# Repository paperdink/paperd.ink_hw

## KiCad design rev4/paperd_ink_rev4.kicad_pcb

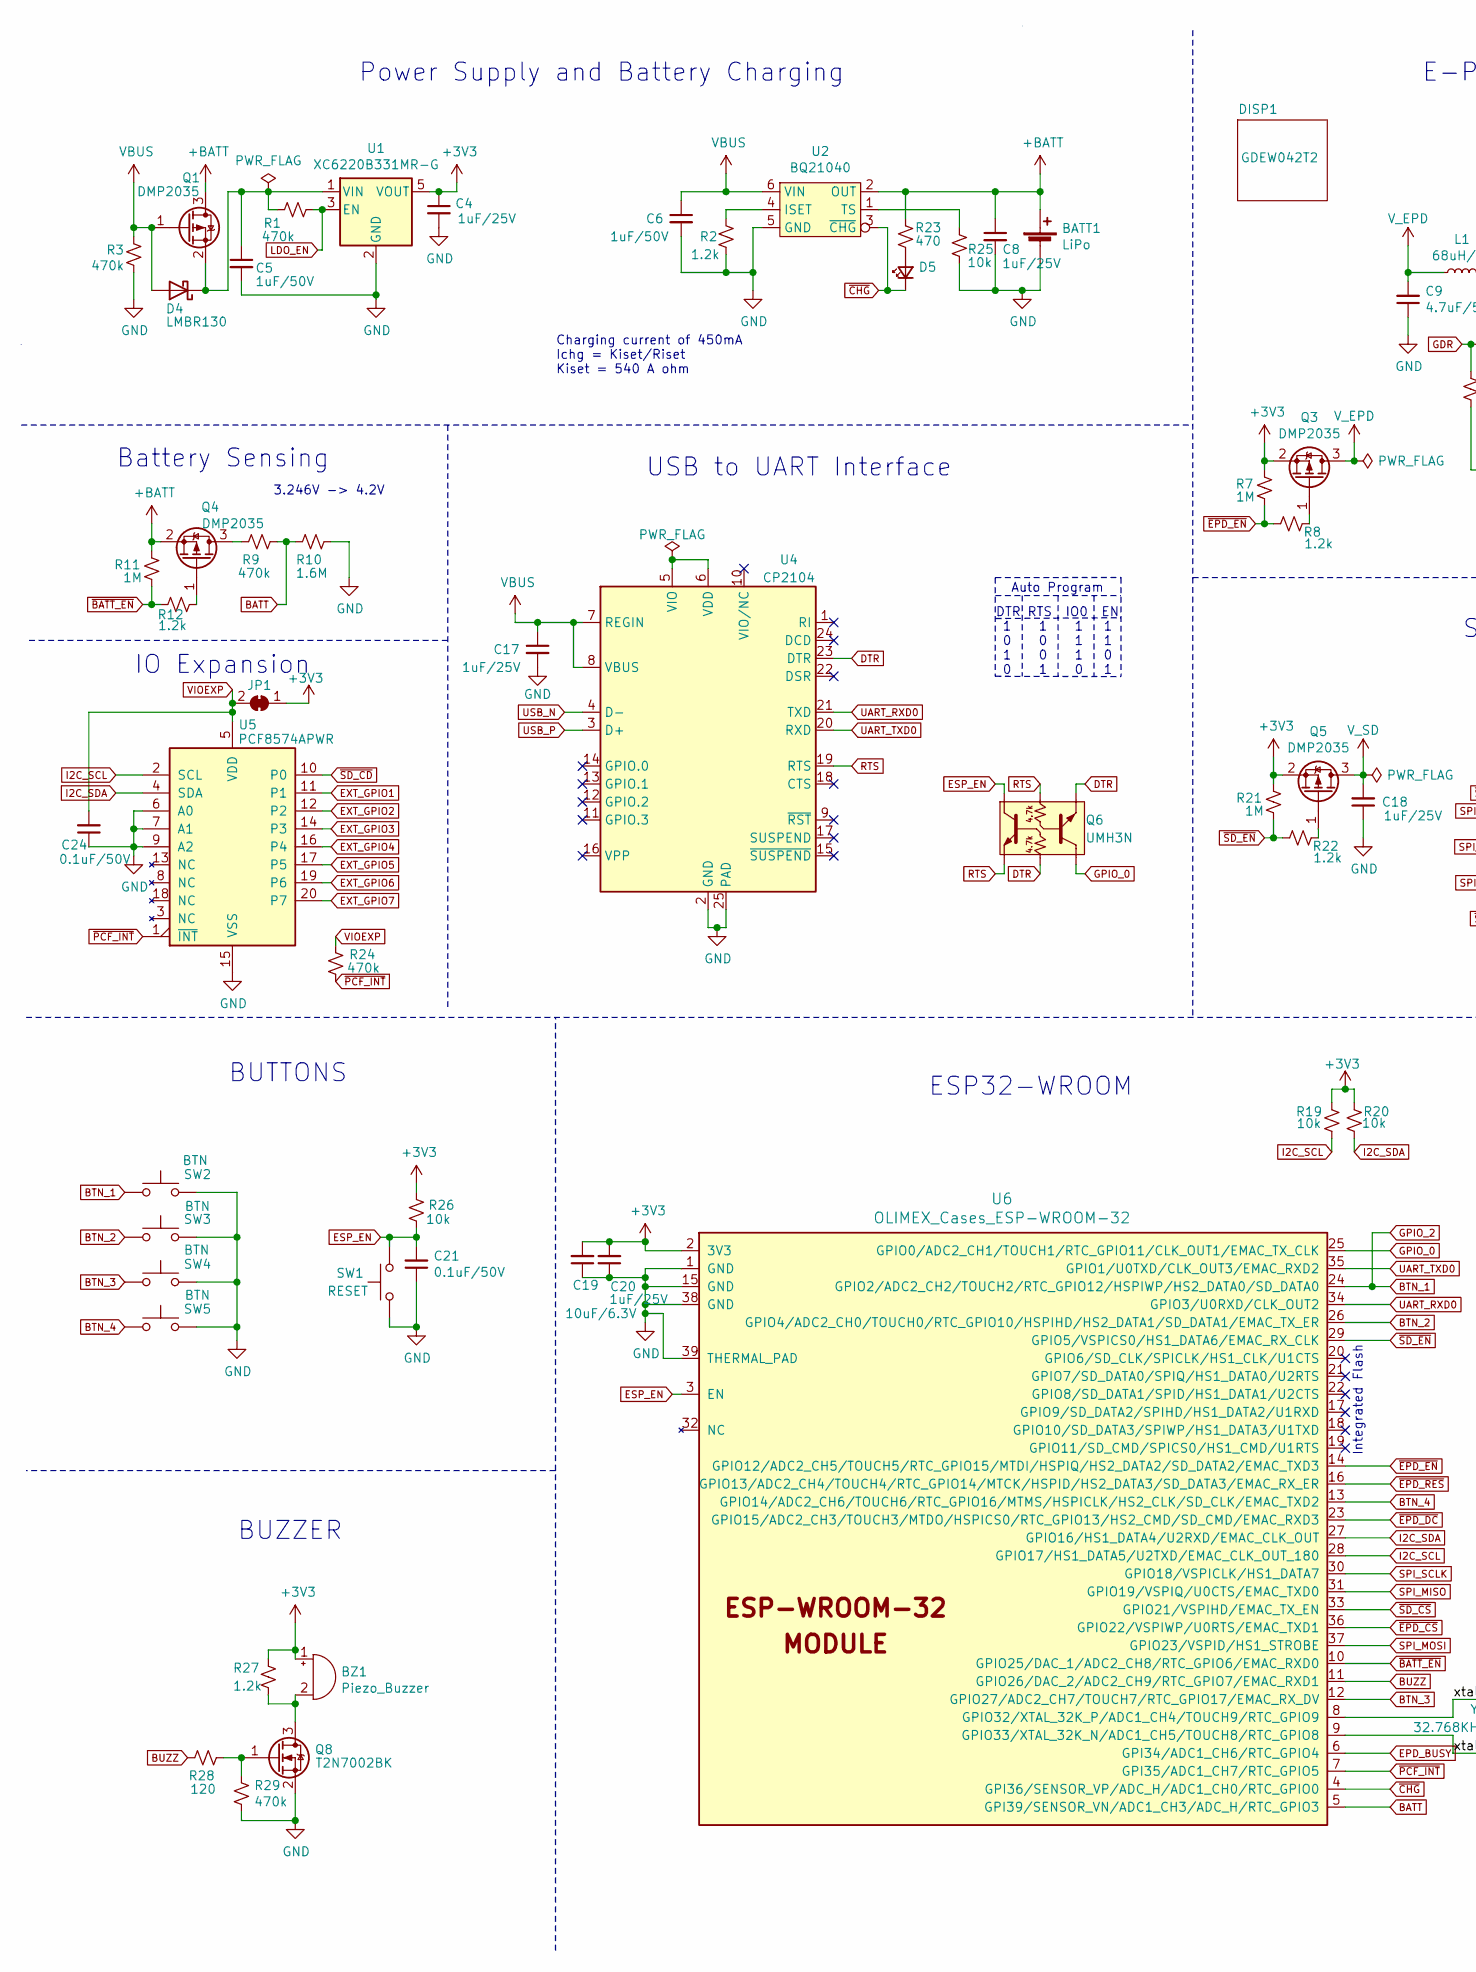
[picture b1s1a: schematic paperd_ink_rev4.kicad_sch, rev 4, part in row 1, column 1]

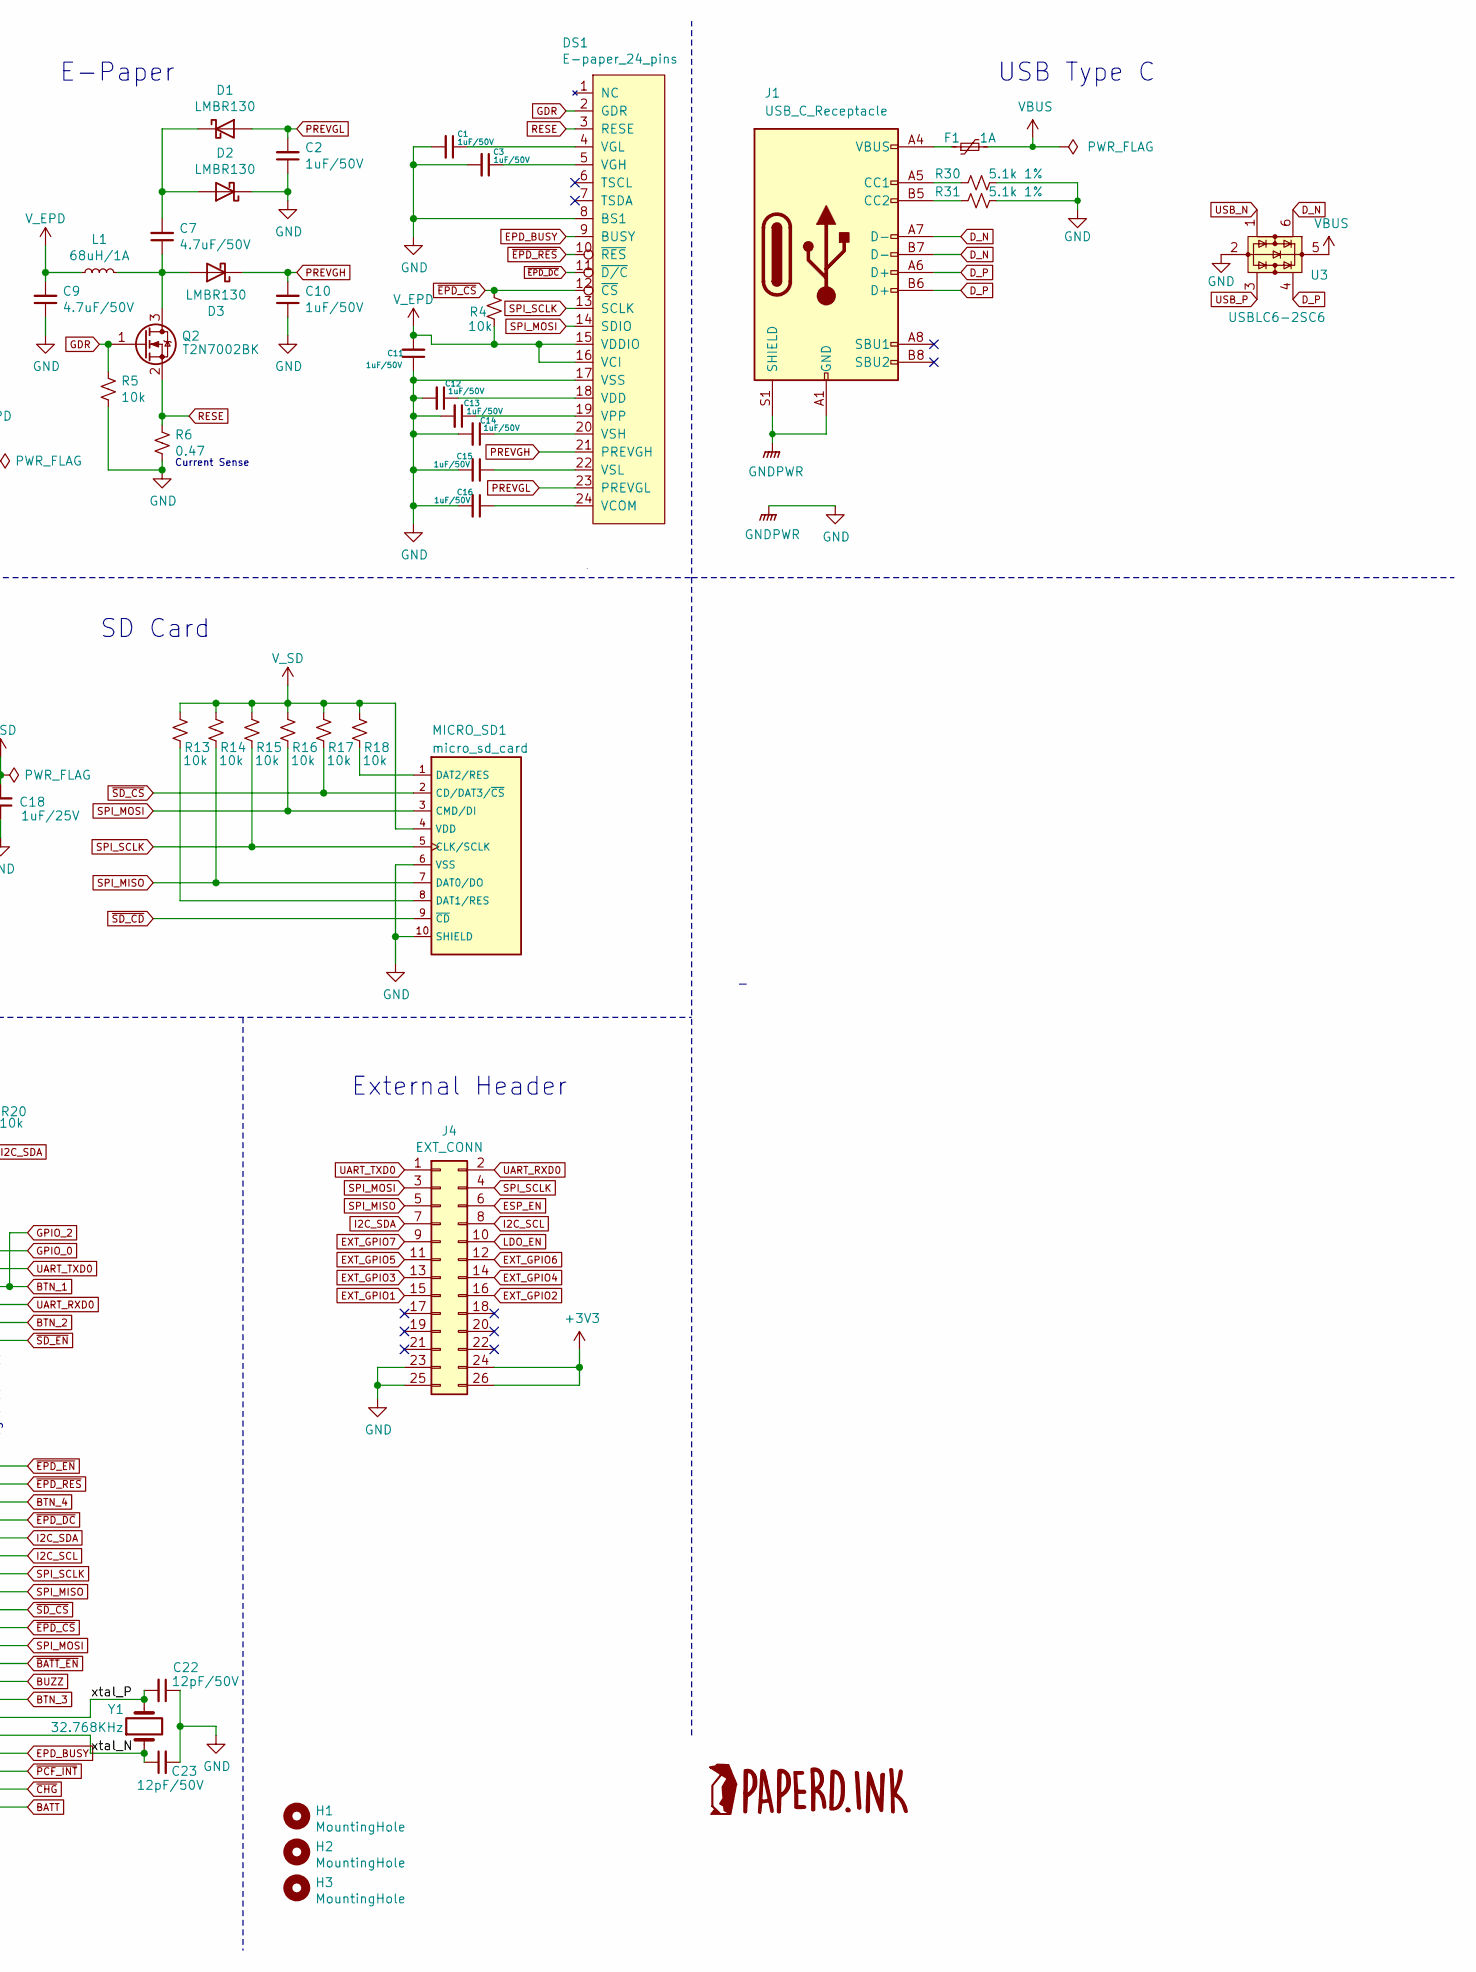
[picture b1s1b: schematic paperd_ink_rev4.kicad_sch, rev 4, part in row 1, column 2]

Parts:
BATT1: LiPo; JST_PH_B2B-PH-SM4-TB_1x02-1MP_P2.00mm_Vertical; MPN C47647; LCSC C47647
BZ1: Piezo_Buzzer; KLJ-1230; MPN KLJ-1230; LCSC C201042
C1, C2, C3, C5, C6, C10, C11, C12, C13, C14, C15, C16: 1uF/50V; C_0603_1608Metric; MPN CL10A105KB8NNNC; LCSC C15849
C4, C8, C17, C18, C20: 1uF/25V; C_0402_1005Metric; MPN CL05A105KA5NQNC; LCSC C52923
C7, C9: 4.7uF/50V; C_0805_2012Metric; MPN CL21A475KBQNNNE; LCSC C98192
C19: 10uF/6.3V; C_0402_1005Metric; MPN CL05A106MQ5NUNC; LCSC C15525
C21, C24: 0.1uF/50V; C_0402_1005Metric; MPN CC0402KRX5R9BB104; LCSC C105882
C22, C23: 12pF/50V; C_0402_1005Metric; MPN 0402CG120J500NT; LCSC C1547
D1, D2, D3, D4: LMBR130; D_SOD-123; MPN LMBR130T1G; LCSC C48974
D5: LED_Small; TJ-S1706SW6TGLC2R-A5; MPN TJ-S1706SW6TGLC2R-A5; LCSC C273612
DISP1: GDEW042T2; MPN GDEW042T2
DS1: E-paper_24_pins; 24 pin FPC connector; MPN 0.5-24P XGXJ-H2.0 119; LCSC C2858298
F1: 1A; Fuse_0805_2012Metric; MPN MF-PSMF050X-2; LCSC C116170
H1, H2, H3: MountingHole; JLCPCB_Tooling_Hole
J1: USB_C_Receptacle; USB_C_Receptacle_HRO_TYPE-C-31-M-12; MPN 918-418K2023S40019; LCSC C709035
J4: EXT_CONN; PinHeader_2x13_P2.54mm_Vertical_SMD; MPN DNP
JP1: IO_EXP_JMP; SolderJumper-2_P1.3mm_Bridged_RoundedPad1.0x1.5mm; MPN DNP
L1: 68uH/1A; L_1210_3225Metric; MPN CBC3225T680MR; LCSC C223227
MICRO_SD1: micro_sd_card; HYC77-TF09-200; MPN HYC77-TF09-200; LCSC C341092
Q1, Q3, Q4, Q5: DMP2035; SOT-23; MPN DMP2035U-7; LCSC C110499
Q2, Q8: T2N7002BK; SOT-23; MPN T2N7002BK,LM; LCSC C146372
Q6: UMH3N; SOT-363_SC-70-6; MPN UMH3N; LCSC C62892
R1, R3, R9, R24, R29: 470k; R_0402_1005Metric; MPN WR04X4703FTL; LCSC C168230
R2, R8, R12, R22, R27: 1.2k; R_0402_1005Metric; MPN WR04X122JTL; LCSC C170376
R4, R5, R13, R14, R15, R16, R17, R18, R19, R20, R25, R26: 10k; R_0402_1005Metric; MPN RMS04JT103; LCSC C208959
R6: 0.47; R_0603_1608Metric; MPN 0603WAF470LT5E; LCSC C23411
R7, R11, R21: 1M; R_0402_1005Metric; MPN RMS04FT1004; LCSC C208777
R10: 1.6M; R_0402_1005Metric; MPN AC0402FR-071M6L; LCSC C226874
R23: 470; R_0402_1005Metric; MPN 0402WGJ0471TCE; LCSC C25167
R28: 120; R_0402_1005Metric; MPN WR04X1200FTL; LCSC C168196
R30, R31: 5.1k 1%; R_0402_1005Metric; MPN WR04X5101FTL; LCSC C163833
SW1: RESET; K2-1822SA-A3DW-06; MPN K2-1822SA-A3DW-06; LCSC C128937
SW2, SW3, SW4, SW5: BTN; TS36CA-0.7; MPN TS36CA-0.7; LCSC C412365
U1: XC6220B331MR-G; SOT-23-5; MPN XC6220B331MR-G; LCSC C86534
U2: BQ21040; SOT-23-6; MPN BQ21040DBVR; LCSC C202311
U3: USBLC6-2SC6; SOT-23-6; MPN USBLC6-2SC6; LCSC C558442
U4: CP2104; QFN-24-1EP_4x4mm_P0.5mm_EP2.6x2.6mm; MPN CP2104-F03-GMR; LCSC C47742
U5: PCF8574APWR; TSSOP-20_4.4x6.5mm_P0.65mm; MPN PCF8574TS/3,118; LCSC C57790
U6: OLIMEX_Cases_ESP-WROOM-32; ESP32-WROOM-32; MPN ESP32-WROOM-32D; LCSC C473012
Y1: 32.768KHz; Q13FC1350000400; MPN Q13FC1350000400; LCSC C32346

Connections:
+3V3: BZ1.1 (-), C4.1, C19.2, C20.2, J4.24, J4.26, JP1.1 (A), Q3.2 (S), Q5.2 (S), R7.2, R19.2, R20.2, R21.2, R26.1, R27.1, U1.5 (VOUT), U6.2 (3V3)
+BATT: BATT1.1 (+), C8.1, Q1.3 (D), Q4.2 (S), R11.2, R23.1, U2.2 (OUT)
/xtal_N: C23.1, U6.9 (GPIO33/XTAL_32K_N/ADC1_CH5/TOUCH8/RTC_G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), Y1.1
/xtal_P: C22.2, U6.8 (GPIO32/XTAL_32K_P/ADC1_CH4/TOUCH9/RTC_G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), Y1.2
BATT: R9.1, R10.2, U6.5 (GPI39/SENSOR_VN/ADC1_CH3/ADC_H/RTC_GPIO3)
BTN_1: SW2.2, U6.24 (GPIO2/ADC2_CH2/TOUCH2/RTC_GPIO12/HSPIWP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)
BTN_2: SW3.2, U6.26 (GPIO4/ADC2_CH0/TOUCH0/RTC_GPIO10/HSPIHD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)
BTN_3: SW4.2, U6.12 (GPIO27/ADC2_CH7/TOUCH7/RTC_GPIO17/EMAC_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)
BTN_4: SW5.2, U6.13 (GPIO14/ADC2_CH6/TOUCH6/RTC_GPIO16/MTMS/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)
BUZZ: R28.2, U6.11 (GPIO26/DAC_2/ADC2_CH9/RTC_GPIO7/EMAC_RX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)
DTR: Q6.2 (B1), Q6.4 (E2), U4.23 (DTR)
D_N: J1.A7 (D-), J1.B7 (D-), U3.6 (IO1)
D_P: J1.A6 (D+), J1.B6 (D+), U3.4 (IO2)
EPD_BUSY: DS1.9 (BUSY), U6.6 (GPI34/ADC1_CH6/RTC_GPIO4)
ESP_EN: C21.2, J4.6, Q6.6 (C1), R26.2, SW1.2, U6.3 (EN)
EXT_GPIO1: J4.15, U5.11 (P1)
EXT_GPIO2: J4.16, U5.12 (P2)
EXT_GPIO3: J4.13, U5.14 (P3)
EXT_GPIO4: J4.14, U5.16 (P4)
EXT_GPIO5: J4.11, U5.17 (P5)
EXT_GPIO6: J4.12, U5.19 (P6)
EXT_GPIO7: J4.9, U5.20 (P7)
GDR: DS1.2 (GDR), Q2.1 (G), R5.1
GND: BATT1.2 (-), C1.2, C2.1, C3.2, C4.2, C5.2, C6.2, C8.2, C9.1, C10.1, C11.1, C12.2, C13.2, C14.2, C15.2, C16.2, C17.2, C18.1, C19.1, C20.1, C21.1, C22.1, C23.2, C24.1, D2.1 (K), DS1.8 (BS1), DS1.17 (VSS), J1.A1 (GND), J1.A12 (GND), J1.B1 (GND), J1.B12 (GND), J1.S1 (SHIELD), J4.23, J4.25, MICRO_SD1.6 (VSS), MICRO_SD1.10 (SHIELD), Q8.2 (S), R2.2, R3.2, R5.2, R6.2, R10.1, R25.2, R29.2, R30.1, R31.1, SW1.1, SW2.1, SW3.1, SW4.1, SW5.1, U1.2 (GND), U2.5 (GND), U3.2 (GND), U4.2 (GND), U4.25 (PAD), U5.6 (A0), U5.7 (A1), U5.9 (A2), U5.15 (VSS), U6.1 (GND), U6.15 (GND), U6.38 (GND), U6.39 (THERMAL_PAD)
GPIO_0: Q6.3 (C2), U6.25 (GPIO0/ADC2_CH1/TOUCH1/RTC_GPIO11/CLK_OU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)
I2C_SCL: J4.8, R19.1, U5.2 (SCL), U6.28 (GPIO17/HS1_DATA5/U2TXD/EMAC_CLK_OUT_180)
I2C_SDA: J4.7, R20.1, U5.4 (SDA), U6.27 (GPIO16/HS1_DATA4/U2RXD/EMAC_CLK_OUT)
LDO_EN: J4.10, R1.2, U1.3 (EN)
unnamed: BZ1.2 (+), Q8.3 (D), R27.2
unnamed: C1.1, DS1.4 (VGL)
unnamed: C3.1, DS1.5 (VGH)
unnamed: C5.1, D4.1 (K), Q1.2 (S), R1.1, U1.1 (VIN)
unnamed: C7.1, D3.2 (A), L1.2, Q2.3 (D)
unnamed: C7.2, D1.1 (K), D2.2 (A)
unnamed: C12.1, DS1.18 (VDD)
unnamed: C13.1, DS1.19 (VPP)
unnamed: C14.1, DS1.20 (VSH)
unnamed: C15.1, DS1.22 (VSL)
unnamed: C16.1, DS1.24 (VCOM)
unnamed: D5.2 (A), R23.2
unnamed: F1.1, J1.A4 (VBUS), J1.A9 (VBUS), J1.B4 (VBUS), J1.B9 (VBUS)
unnamed: J1.A5 (CC1), R30.2
unnamed: J1.B5 (CC2), R31.2
unnamed: MICRO_SD1.1 (DAT2/RES), R18.2
unnamed: MICRO_SD1.8 (DAT1/RES), R13.2
unnamed: Q3.1 (G), R8.1
unnamed: Q4.1 (G), R12.1
unnamed: Q4.3 (D), R9.2
unnamed: Q5.1 (G), R22.1
unnamed: Q8.1 (G), R28.1, R29.1
unnamed: R2.1, U2.4 (ISET)
unnamed: R25.1, U2.1 (TS)
unnamed: U4.5 (VIO), U4.6 (VDD)
PREVGH: C10.2, D3.1 (K), DS1.21 (PREVGH)
PREVGL: C2.2, D1.2 (A), DS1.23 (PREVGL)
RESE: DS1.3 (RESE), Q2.2 (S), R6.1
RTS: Q6.1 (E1), Q6.5 (B2), U4.19 (RTS)
SPI_MISO: J4.5, MICRO_SD1.7 (DAT0/DO), R14.2, U6.31 (GPIO19/VSPIQ/U0CTS/EMAC_TXD0)
SPI_MOSI: DS1.14 (SDIO), J4.3, MICRO_SD1.3 (CMD/DI), R16.2, U6.37 (GPIO23/VSPID/HS1_STROBE)
SPI_SCLK: DS1.13 (SCLK), J4.4, MICRO_SD1.5 (CLK/SCLK), R15.2, U6.30 (GPIO18/VSPICLK/HS1_DATA7)
UART_RXD0: J4.2, U4.21 (TXD), U6.34 (GPIO3/U0RXD/CLK_OUT2)
UART_TXD0: J4.1, U4.20 (RXD), U6.35 (GPIO1/U0TXD/CLK_OUT3/EMAC_RXD2)
USB_N: U3.1 (IO1), U4.4 (D-)
USB_P: U3.3 (IO2), U4.3 (D+)
VBUS: C6.1, C17.1, D4.2 (A), F1.2, Q1.1 (G), R3.1, U2.6 (VIN), U3.5 (VBUS), U4.7 (REGIN), U4.8 (VBUS)
VIOEXP: C24.2, JP1.2 (B), R24.2, U5.5 (VDD)
V_EPD: C9.2, C11.2, DS1.15 (VDDIO), DS1.16 (VCI), L1.1, Q3.3 (D), R4.2
V_SD: C18.2, MICRO_SD1.4 (VDD), Q5.3 (D), R13.1, R14.1, R15.1, R16.1, R17.1, R18.1
~BATT_EN: R11.1, R12.2, U6.10 (GPIO25/DAC_1/ADC2_CH8/RTC_GPIO6/EMAC_RX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)
~CHG: D5.1 (K), U2.3 (~CHG), U6.4 (GPI36/SENSOR_VP/ADC_H/ADC1_CH0/RTC_GPIO0)
~EPD_CS: DS1.12 (~CS), R4.1, U6.36 (GPIO22/VSPIWP/U0RTS/EMAC_TXD1)
~EPD_DC: DS1.11 (~D/C), U6.23 (GPIO15/ADC2_CH3/TOUCH3/MTDO/HSPICS0/RTC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)
~EPD_EN: R7.1, R8.2, U6.14 (GPIO12/ADC2_CH5/TOUCH5/RTC_GPIO15/MTDI/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)
~EPD_RES: DS1.10 (~RES), U6.16 (GPIO13/ADC2_CH4/TOUCH4/RTC_GPIO14/MTCK/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)
~PCF_INT: R24.1, U5.1 (~INT), U6.7 (GPI35/ADC1_CH7/RTC_GPIO5)
~SD_CD: MICRO_SD1.9 (~CD), U5.10 (P0)
~SD_CS: MICRO_SD1.2 (CD/DAT3/~CS), R17.2, U6.33 (GPIO21/VSPIHD/EMAC_TX_EN)
~SD_EN: R21.1, R22.2, U6.29 (GPIO5/VSPICS0/HS1_DATA6/EMAC_RX_CLK)

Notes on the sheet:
DTR RTS IO0 EN 1 1 1 1 0 0 1 1 1 0 1 0 0 1 0 1
Charging current of 450mA Ichg = Kiset/Riset Kiset = 540 A ohm
Auto Program
3.246V -> 4.2V
External Header
Battery Sensing
Integrated Flash
E-Paper
BUTTONS
USB Type C
SD Card
Power Supply and Battery Charging
Current Sense
USB to UART Interface
IO Expansion
ESP32-WROOM
BUZZER

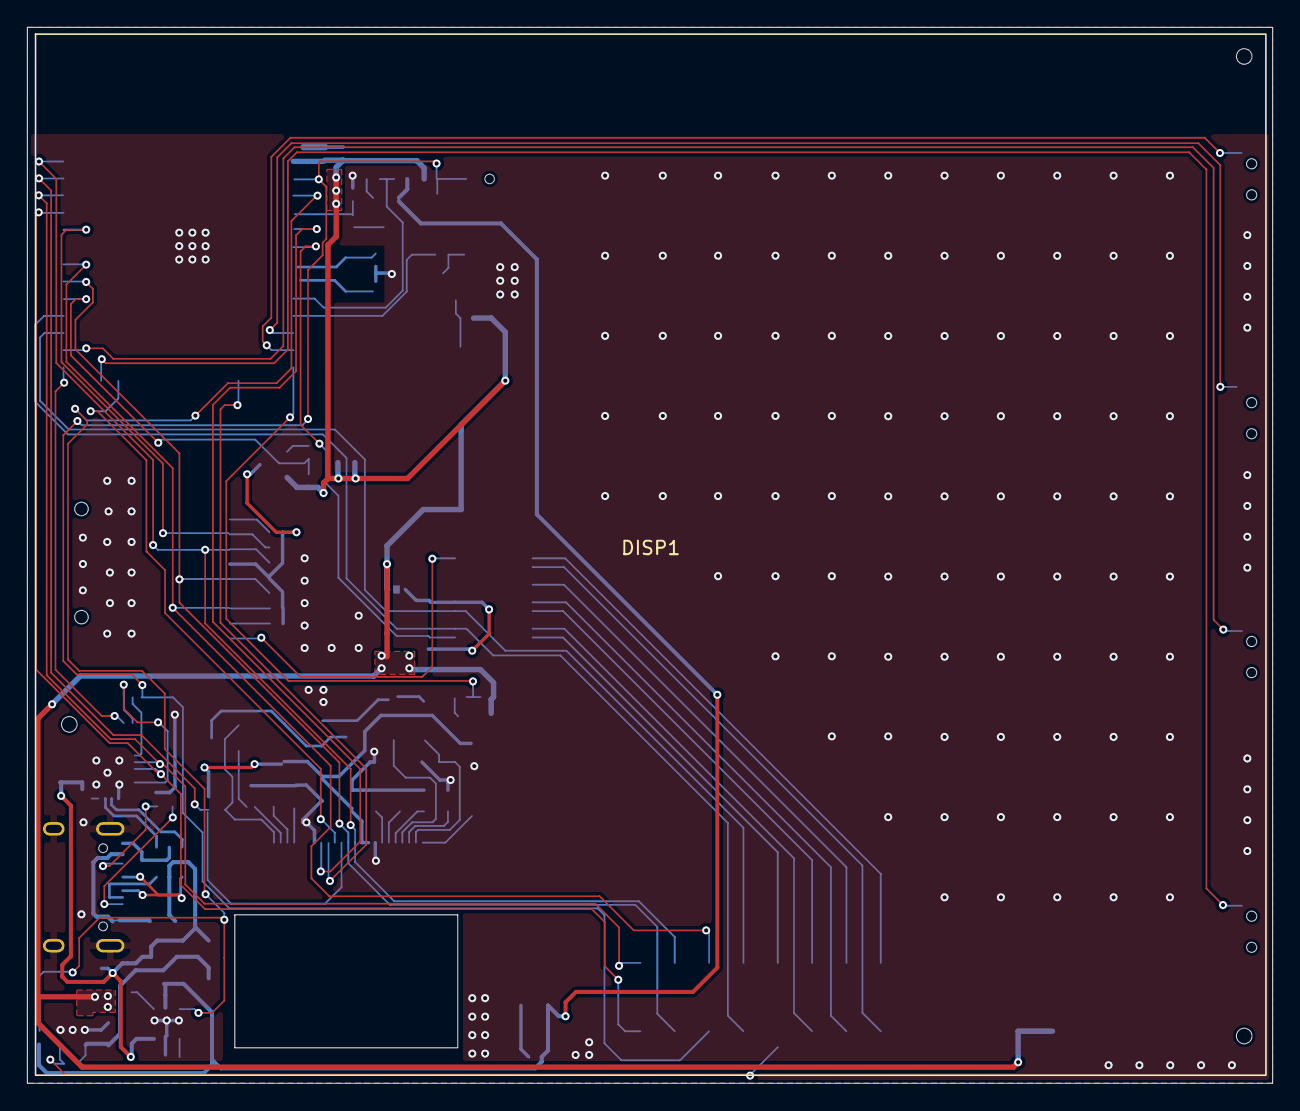
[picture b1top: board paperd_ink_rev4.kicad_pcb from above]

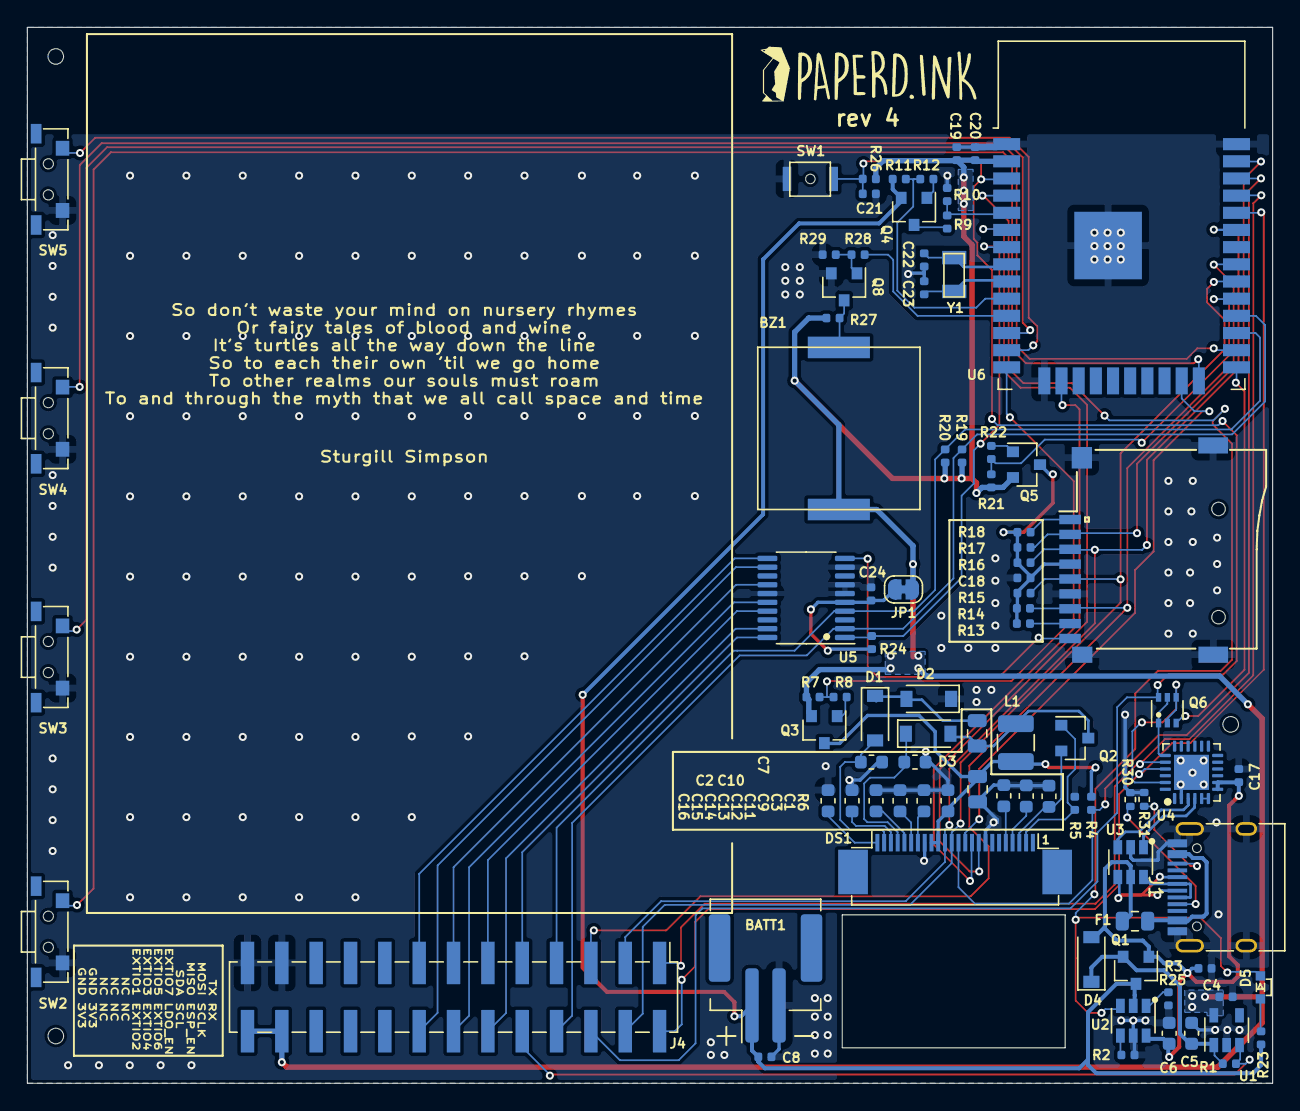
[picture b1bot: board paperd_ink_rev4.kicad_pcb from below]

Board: 2 copper layers, 92.1 x 78.1 mm, 92 parts (91 on the bottom side), 78 nets.

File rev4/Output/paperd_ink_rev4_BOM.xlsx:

Source: | /home/rgujju/Documents/paperd.ink/paperdink_new/Electronics/rev4/paperd_ink_rev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
Date: | Mon 18 Jul 2022 09:41:19 PM CDT
Tool: | Eeschema (6.0.2)
Generator: | /usr/share/kicad/plugins/bom_csv_grouped_by_value.py
Component Count: | 89
Collated Components:
Item | Qty | Reference(s) | Value | LibPart | Footprint | Datasheet | Alternate 1 | Alternate 1 MPN | LCSC | Link | MPN | Manufacturer
1 | 1 | BATT1 | Battery connector | Device:Battery_Cell | Connector_JST:JST_PH_B2B-PH-SM4-TB_1x02-1MP_P2.00mm_Vertical | ~ |  |  | C47647 | https://lcsc.com/product-detail/Wire-To-Board-Wire-To-Wire-C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 | C47647 | BOOMELE(Boom Precision Elec)
2 | 1 | BZ1 | Piezo_Buzzer | Device:Buzzer | 021_labs:KLJ-1230 |  |  |  | C201042 |  | KLJ-1230 | KELIKING
3 | 12 | C1, C2, C3, C5, C6, C10, C11, C12, C13, C14, C15, C16 | 1uF/50V | Device:C_Small | Capacitor_SMD:C_0603_1608Metric |  |  |  | C15849 |  | CL10A105KB8NNNC | Samsung Electro-Mechanics
4 | 5 | C4, C8, C17, C18, C20 | 1uF/25V | Device:C_Small | Capacitor_SMD:C_0402_1005Metric |  |  |  | C52923 |  | CL05A105KA5NQNC | Samsung Electro-Mechanics
5 | 2 | C7, C9 | 4.7uF/50V | Device:C_Small | Capacitor_SMD:C_0805_2012Metric |  |  |  | C98192 |  | CL21A475KBQNNNE | Samsung Electro-Mechanics
6 | 1 | C19 | 10uF/6.3V | Device:C_Small | Capacitor_SMD:C_0402_1005Metric |  |  |  | C15525 |  | CL05A106MQ5NUNC | Samsung Electro-Mechanics
7 | 2 | C21, C24 | 0.1uF/50V | Device:C_Small | Capacitor_SMD:C_0402_1005Metric |  |  |  | C105882 |  | CC0402KRX5R9BB104 | YAGEO
8 | 2 | C22, C23 | 12pF/50V | Device:C_Small | Capacitor_SMD:C_0402_1005Metric |  |  |  | C1547 |  | 0402CG120J500NT | FH(Guangdong Fenghua Advanced Tech)
9 | 4 | D1, D2, D3, D4 | LMBR130 | Diode:MBR0530 | Diode_SMD:D_SOD-123 |  |  |  | C48974 |  | LMBR130T1G | LRC
10 | 1 | D5 | LED_Small | Device:LED_Small | 021_labs:TJ-S1706SW6TGLC2R-A5 | ~ |  |  | C273612 |  | TJ-S1706SW6TGLC2R-A5 | TOGIALED
11 | 1 | DISP1 | GDEW042T2 | 021_labs:E-paper | 021_labs:GDEW042T2 |  |  |  |  |  | GDEW042T2 | Good-Display
12 | 1 | DS1 | E-paper_24_pins | 021_labs:E-paper_24_pins | 021_labs:24 pin FPC connector | https://datasheet.lcsc.com/lcsc/2108150230_SHOU-HAN-0-5-24P-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 |  |  | C2858298 |  | 0.5-24P XGXJ-H2.0 119 | SHOU HAN
13 | 1 | F1 | 1A | Device:Polyfuse_Small | Fuse:Fuse_0805_2012Metric | ~ |  |  | C116170 |  | MF-PSMF050X-2 | BOURNS
14 | 1 | J1 | USB_C_Receptacle | Connector:USB_C_Receptacle_USB2.0 | Connector_USB:USB_C_Receptacle_HRO_TYPE-C-31-M-12 | https://www.usb.org/sites/default/files/documents/usb_type-c.zip | C2965608 | TYPE-C16P3MDDGP073 | C709035 | https://lcsc.com/product-detail/USB-Connectors_Jing-Extensio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 | 918-418K2023S40019 | Jing Extension of the Electronic Co.
15 | 1 | J4 | EXT_CONN | Connector_Generic:Conn_02x13_Odd_Even | Connector_PinHeader_2.54mm:PinHeader_2x13_P2.54mm_Vertical_SMD |  |  |  |  |  | DNP
16 | 1 | JP1 | IO_EXP_JMP | Jumper:SolderJumper_2_Bridged | Jumper:SolderJumper-2_P1.3mm_Bridged_RoundedPad1.0x1.5mm |  |  |  |  |  | DNP
17 | 1 | L1 | 68uH/1A | Device:L_Small | Inductor_SMD:L_1210_3225Metric |  |  |  | C223227 |  | CBC3225T680MR | Taiyo Yuden
18 | 1 | MICRO_SD1 | micro_sd_card | 021_labs:micro_sd_card | 021_labs:HYC77-TF09-200 |  |  |  | C341092 |  | HYC77-TF09-200 | HOAUC
19 | 4 | Q1, Q3, Q4, Q5 | DMP2035 | 021_labs:DMP2035 | Package_TO_SOT_SMD:SOT-23 |  |  |  | C110499 |  | DMP2035U-7 | Diodes Incorporated
20 | 2 | Q2, Q8 | T2N7002BK | 021_labs:NTA4153NT1G | Package_TO_SOT_SMD:SOT-23 |  |  |  | C146372 |  | T2N7002BK,LM | TOSHIBA
21 | 1 | Q6 | UMH3N | 021_labs:UMH3N | Package_TO_SOT_SMD:SOT-363_SC-70-6 |  |  |  | C62892 |  | UMH3N | Changjiang Electronics Tech (CJ)
22 | 5 | R1, R3, R9, R24, R29 | 470k | Device:R_Small_US | Resistor_SMD:R_0402_1005Metric | ~ |  |  | C168230 |  | WR04X4703FTL | Walsin Tech Corp
23 | 5 | R2, R8, R12, R22, R27 | 1.2k | Device:R_Small_US | Resistor_SMD:R_0402_1005Metric | ~ |  |  | C170376 |  | WR04X122JTL | Walsin Tech Corp
24 | 12 | R4, R5, R13, R14, R15, R16, R17, R18, R19, R20, R25, R26 | 10k | Device:R_Small_US | Resistor_SMD:R_0402_1005Metric | ~ |  |  | C208959 |  | RMS04JT103 | TA-I Tech
25 | 1 | R6 | 0.46999999999999997 | Device:R_Small_US | Resistor_SMD:R_0603_1608Metric | ~ |  |  | C23411 |  | 0603WAF470LT5E | UNI-ROYAL(Uniroyal Elec)
26 | 3 | R7, R11, R21 | 1M | Device:R_Small_US | Resistor_SMD:R_0402_1005Metric | ~ |  |  | C208777 |  | RMS04FT1004 | TA-I Tech
27 | 1 | R10 | 1.6M | Device:R_Small_US | Resistor_SMD:R_0402_1005Metric | ~ |  |  | C226874 |  | AC0402FR-071M6L | YAGEO
28 | 1 | R23 | 470 | Device:R_Small_US | Resistor_SMD:R_0402_1005Metric | ~ |  |  | C25167 |  | 0402WGJ0471TCE | UNI-ROYAL(Uniroyal Elec)
29 | 1 | R28 | 120 | Device:R_Small_US | Resistor_SMD:R_0402_1005Metric | ~ |  |  | C168196 |  | WR04X1200FTL | Walsin Tech Corp
30 | 2 | R30, R31 | 5.1k 1% | Device:R_Small_US | Resistor_SMD:R_0402_1005Metric | ~ |  |  | C163833 |  | WR04X5101FTL | Walsin Tech Corp
31 | 1 | SW1 | RESET | Switch:SW_Push | 021_labs:K2-1822SA-A3DW-06 |  |  |  | C128937 |  | K2-1822SA-A3DW-06 | Korean Hroparts Elec
32 | 4 | SW2, SW3, SW4, SW5 | BTN | Switch:SW_Push | 021_labs:TS36CA-0.7 |  |  |  | C412365 |  | TS36CA-0.7 | SHOU HAN
33 | 1 | U1 | XC6220B331MR-G | Regulator_Linear:AP2112K-3.3 | Package_TO_SOT_SMD:SOT-23-5 | https://www.diodes.com/assets/Datasheets/AP2112.pdf |  |  | C86534 |  | XC6220B331MR-G | Torex Semicon
34 | 1 | U2 | BQ21040 | 021_labs:BQ21040 | Package_TO_SOT_SMD:SOT-23-6 |  |  |  | C202311 |  | BQ21040DBVR | Texas Instruments
35 | 1 | U3 | USBLC6-2SC6 | 021_labs:USBLC6-2SC6 | Package_TO_SOT_SMD:SOT-23-6 |  |  |  | C558442 |  | USBLC6-2SC6 | STM/Tech Public
36 | 1 | U4 | CP2104 | 021_labs:CP2104 | Package_DFN_QFN:QFN-24-1EP_4x4mm_P0.5mm_EP2.6x2.6mm |  |  |  | C47742 |  | CP2104-F03-GMR | Silicon Labs
37 | 1 | U5 | PCF8574APWR | 021_labs:PCF8574APWR | Package_SO:TSSOP-20_4.4x6.5mm_P0.65mm |  |  |  | C57790 |  | PCF8574TS/3,118 | NXP Semicon
38 | 1 | U6 | OLIMEX_Cases_ESP-WROOM-32 | 021_labs:ESP-WROOM-32 | RF_Module:ESP32-WROOM-32 |  |  |  | C473012 |  | ESP32-WROOM-32D | Espressif Systems
39 | 1 | Y1 | 32.768KHz | Device:Crystal | 021_labs:Q13FC1350000400 |  |  |  | C32346 |  | Q13FC1350000400 | Seiko Epson

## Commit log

2022-04-13 Added License
2022-04-13 Added hardware files
2022-07-19 Added paperd.ink rev4
2022-07-19 Added BOM
